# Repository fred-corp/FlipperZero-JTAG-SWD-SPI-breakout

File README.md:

# Flipper Zero JTAG/SWD/SPI breakout

A simple breakout board to connect a Flipper Zero to JTAG/SWD/SPI targets.

OSHW ID : [BE000022](https://certification.oshwa.org/be000022.html)

## Table of Contents

- [Features](#features)
  - [Compatible Apps](#compatible-apps)
  - [Pin selection](#pin-selection)
- [Pinouts](#pinouts)
  - [Flipper Zero GPIO header](#flipper-zero-gpio-header)
  - [20 pin JTAG 2x10 0.1" header](#20-pin-jtag-2x10-01-header)
  - [10 pin JTAG/SWD 2x5 0.1" and 0.05" header](#10-pin-jtagswd-2x5-01-and-005-header)
  - [6 pin SWD 2x3 0.1" header](#6-pin-swd-2x3-01-header)
  - [6 pin SPI 2x3 0.1" header](#6-pin-spi-2x3-01-header)
  - [5 pin UART 1x5 0.1" header](#5-pin-uart-1x5-01-header)
- [Usage](#usage)
- [Building Instructions](#building-instructions)
- [Sources](#sources)
- [License & Acknowledgements](#license--acknowledgements)

## Features

Convert the Flipper Zero's GPIO port into standard headers for JTAG, SWD, SPI, and UART connections.

### Compatible Apps

The board should be compatible with any apps that use the Flipper Zero's GPIO port for JTAG/SWD/SPI communication, though the following where the main targets during development for the pin selection and configuration :

- [DAP Link](https://lab.flipper.net/apps/dap_link) (JTAG/SWD & UART)
- [SWD Probe](https://lab.flipper.net/apps/swd_probe) (SWD)
- [SPI Mem Manager](https://lab.flipper.net/apps/spi_mem_manager) (SPI)
- [SPI-Terminal](https://lab.flipper.net/apps/flipper_spi_terminal) (SPI)
- [UART Terminal](https://lab.flipper.net/apps/uart_terminal) (UART)
- [ESP Flasher](https://lab.flipper.net/apps/esp_flasher) (UART)

> **Note** :  
Not all JTAG signals are used by the Flipper Zero apps, but the board can also be used to convert from a 20-pin ARM JTAG connector from another programmer to 10 or 6 pin headers.  
It can also be used as a SWD interface with the Flipper Zero as a target, by bridging the TCK and TMS signals to GPIO 10 and GPIO 12 via their corresponding solder jumpers. This enables programming/debugging the Flipper Zero itself with an external programmer.

### Pin selection

Depending on the app's requirements, some signals can be connected to different GPIO pins of the Flipper Zero using solder jumpers (see assembly instructions/schematics) :

- The TCK signal can be connected to GPIO 2 or GPIO 10
- The TMS signal can be connected to GPIO 3 or GPIO 12
- The UART TX pin can be connected to GPIO 13 or GPIO 15
- The UART RX pin can be connected to GPIO 14 or GPIO 16
- The SPI CS pin can be connected to GPIO 4

Other pins can be configured with jumper shunts :

- The VTref signal can be connected to 3.3V, 5V, or left floating
- The PWRSel signal can be connected to 5V or GND depending on the target's pinout
- The nTRST signal on the 10 pin headers can be connected to nTRST or left floating (NC)
- The SPI CS signal on the 6 pin SPI header can be connected to GPIO 4 or GPIO 6

## Pinouts

> Note : *Italic* pins are configurable with the solder jumpers

### Flipper Zero GPIO header

| Pin | Signals               |
|-----|-----------------------|
| 1   | 5V                    |
| 2   | SPI-SDO, *JTAG-TCK*   |
| 3   | SPI-SDI, *JTAG-TMS*   |
| 4   | *SPI-CS*, JTAG-nRESET |
| 5   | SPI-SCK, JTAG-TDO     |
| 6   | *SPI-CS*, JTAG-TDI    |
| 7   | NC                    |
| 8   | GND                   |
|     |                       |
| 9   | 3.3V                  |
| 10  | *JTAG-TCK*            |
| 11  | GND                   |
| 12  | *JTAG-TMS*            |
| 13  | *UART_TX*             |
| 14  | *UART-RX*             |
| 15  | *UART-TX*             |
| 16  | *UART-RX*             |
| 17  | NC                    |
| 18  | GND                   |

### 20 pin JTAG 2x10 0.1" header

| Signal    | Pin | Pin | Signal |
|-----------|-----|-----|--------|
| VTref     | 1   | 2   | NC     |
| nTRST     | 3   | 4   | GND    |
| TDI       | 5   | 6   | GND    |
| TMS       | 7   | 8   | GND    |
| TCK       | 9   | 10  | GND    |
| RTCK      | 11  | 12  | GND    |
| TDO       | 13  | 14  | GND    |
| nRESET    | 15  | 16  | GND    |
| NC        | 17  | 18  | GND    |
| 5V-Supply | 19  | 20  | GND    |

### 10 pin JTAG/SWD 2x5 0.1" and 0.05" header

| Signal     | Pin | Pin | Signal |
|------------|-----|-----|--------|
| VTref      | 1   | 2   | TMS    |
| GND        | 3   | 4   | TCK    |
| *PWRSel*   | 5   | 6   | TDO    |
| RTCK       | 7   | 8   | TDI    |
| *nTRST/NC* | 9   | 10  | nRESET |

### 6 pin SWD 2x3 0.1" header

| Signal | Pin | Pin | Signal |
|--------|-----|-----|--------|
| VTref  | 1   | 2   | TMS    |
| nRESET | 3   | 4   | TCK    |
| GND    | 5   | 6   | TDO    |

### 6 pin SPI 2x3 0.1" header

| Signal | Pin | Pin | Signal  |
|--------|-----|-----|---------|
| SDI    | 1   | 2   | VTref   |
| SCK    | 3   | 4   | SDO     |
| *CS*   | 5   | 6   | GND     |

The CS pin can be connected to GPIO 4 or GPIO 6 of the Flipper Zero, depending on the app's requirements.

### 5 pin UART 1x5 0.1" header

| Pin | Signal |
|-----|--------|
| 1   | 5V     |
| 2   | 3.3V   |
| 3   | TX     |
| 4   | RX     |
| 5   | GND    |

## Usage

> TODO : Add usage instructions for some Flipper Zero apps (e.G. DAP Link, SPI mem manager, etc.)

## Building Instructions

> TODO : Add assembly instructions and wiring diagrams from KiCAD sources (awaiting OSHWA certification).

## Sources

- [Flipper Zero Documentation](https://docs.flipperzero.one/)
- [Segger JTAG pinouts](https://www.segger.com/products/debug-probes/j-link/technology/interface-description/)
- [ARM JTAG/SWD pinouts](https://developer.arm.com/documentation/dui0499/d/ARM-DSTREAM-Target-Interface-Connections/)
- [AVR ISP pinouts](https://www.microchip.com/en-us/development-tool/atavrisp2)

## License & Acknowledgements

Made with ❤️, lots of ☕️, and lack of 🛌  
Published under CreativeCommons BY-SA 4.0

This work is licensed under a [Creative Commons Attribution-ShareAlike 4.0 International License](http://creativecommons.org/licenses/by-sa/4.0/).

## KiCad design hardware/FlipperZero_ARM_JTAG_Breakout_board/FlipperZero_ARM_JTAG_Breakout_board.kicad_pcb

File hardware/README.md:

# Hardware

This folder contains the KiCAD PCB Project files for the FlipperZero ARM JTAG breakout board.

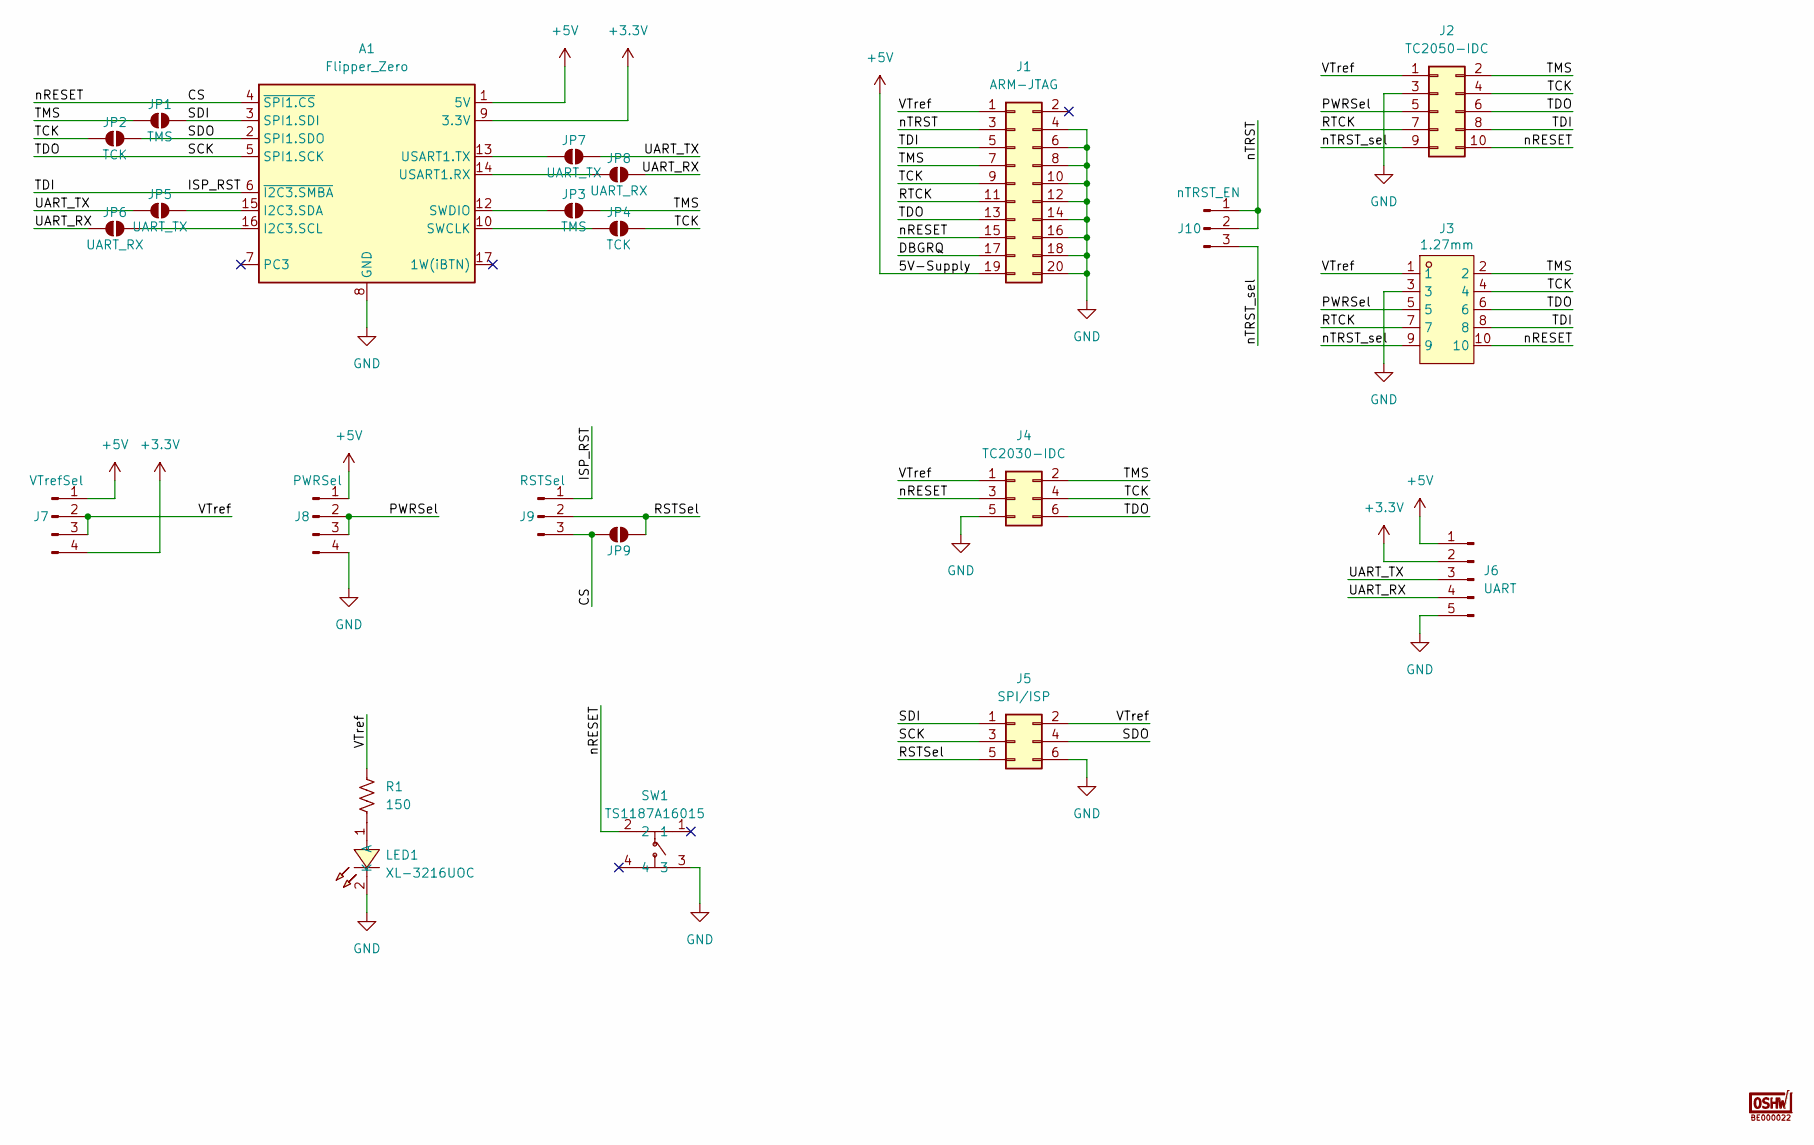
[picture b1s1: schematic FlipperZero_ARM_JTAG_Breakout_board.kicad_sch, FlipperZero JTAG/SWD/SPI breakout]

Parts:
A1: Flipper_Zero; Flipper_Zero_Straight
J1: ARM-JTAG; IDC-Header_2x10_P2.54mm_Vertical; LCSC Part C429961
J2: TC2050-IDC; IDC-Header_2x05_P2.54mm_Vertical; LCSC Part C429962
J3: 1.27mm; IDC-TH_10P-P1.27-V-M-R2-C5-S1.27; LCSC Part C50878437
J4: TC2030-IDC; IDC-Header_2x03_P2.54mm_Vertical; LCSC Part C4749192
J5: SPI/ISP; IDC-Header_2x03_P2.54mm_Vertical; LCSC Part C4749192
J6: UART; PinHeader_1x05_P2.54mm_Vertical
J7: VTrefSel; PinHeader_1x04_P2.54mm_Vertical
J8: PWRSel; PinHeader_1x04_P2.54mm_Vertical
J9: RSTSel; PinHeader_1x03_P2.54mm_Vertical
J10: nTRST_EN; PinHeader_1x03_P2.54mm_Vertical
JP1, JP3, JP9: TMS; JUMPER_SMD_1x2_tiny
JP2, JP4: TCK; JUMPER_SMD_1x2_tiny
JP5, JP7: UART_TX; JUMPER_SMD_1x2_tiny
JP6, JP8: UART_RX; JUMPER_SMD_1x2_tiny
LED1: XL-3216UOC; LED1206-R-RD_ORANGE; LCSC Part C965823
LOGO1: BE000022; OSHW-Certification-Mark-Stacked_8x7mm_SilkMask
R1: 150; R_0603_1608Metric_Pad0.98x0.95mm_HandSolder; LCSC Part C2907103
SW1: TS1187A16015; SW-SMD_4P-L5.2-W5.2-P3.70-LS6.4; LCSC Part C22375382

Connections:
+3.3V: A1.9 (3.3V), J6.2, J7.4
+5V: A1.1 (5V), J1.19, J6.1, J7.1, J8.1
/CS: A1.4 (~SPI1.CS), J1.15, J2.10, J3.10, J4.3, J9.3, JP9.1 (A), SW1.2
/DBGRQ: J1.17
/ISP_RST: A1.6 (~I2C3.SMBA), J1.5, J2.8, J3.8, J9.1
/PWRSel: J2.5, J3.5, J8.2, J8.3
/RSTSel: J5.5, J9.2, JP9.2 (B)
/RTCK: J1.11, J2.7, J3.7
/SCK: A1.5 (SPI1.SCK), J1.13, J2.6, J3.6, J4.6, J5.3
/SDI: A1.3 (SPI1.SDI), J5.1, JP1.1 (A)
/SDO: A1.2 (SPI1.SDO), J5.4, JP2.1 (A)
/TCK: J1.9, J2.4, J3.4, J4.4, JP2.2 (B), JP4.2 (B)
/TMS: J1.7, J2.2, J3.2, J4.2, JP1.2 (B), JP3.2 (B)
/UART_RX: J6.4, JP6.2 (B), JP8.2 (B)
/UART_TX: J6.3, JP5.2 (B), JP7.2 (B)
/VTref: J1.1, J2.1, J3.1, J4.1, J5.2, J7.2, J7.3, R1.1
/nTRST: J1.3, J10.1, J10.2
/nTRST_sel: J2.9, J3.9, J10.3
GND: A1.8 (GND), A1.11 (GND), A1.18 (GND), J1.4, J1.6, J1.8, J1.10, J1.12, J1.14, J1.16, J1.18, J1.20, J2.3, J3.3, J4.5, J5.6, J6.5, J8.4, LED1.2 (K), SW1.3
unnamed: A1.16 (I2C3.SCL), JP6.1 (A)
unnamed: A1.15 (I2C3.SDA), JP5.1 (A)
unnamed: A1.10 (SWCLK), JP4.1 (A)
unnamed: A1.12 (SWDIO), JP3.1 (A)
unnamed: A1.14 (USART1.RX), JP8.1 (A)
unnamed: A1.13 (USART1.TX), JP7.1 (A)
unnamed: LED1.1 (A), R1.2

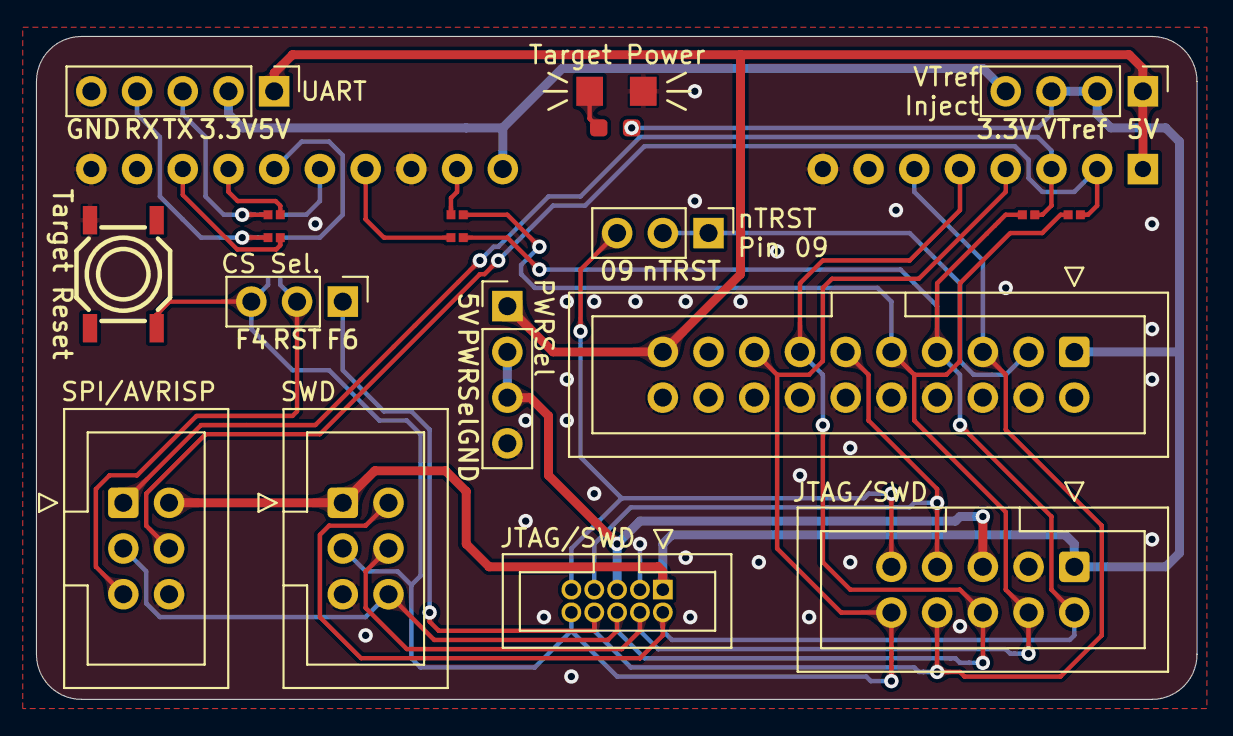
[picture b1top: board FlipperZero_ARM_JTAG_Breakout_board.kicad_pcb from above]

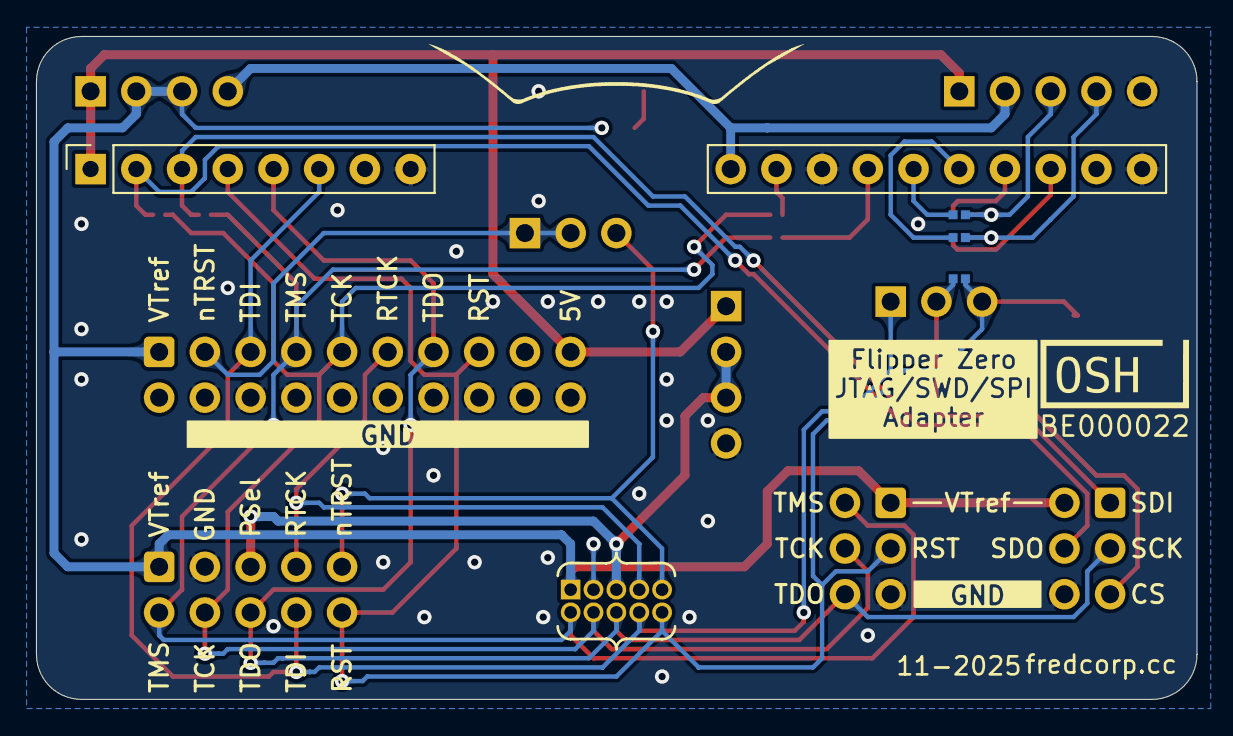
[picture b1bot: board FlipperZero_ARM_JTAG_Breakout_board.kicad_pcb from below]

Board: 2 copper layers, 64.5 x 36.8 mm, 24 parts (5 on the bottom side), 25 nets.

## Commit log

2025-11-10 added trinity of git repo files
2025-11-10 added files to gitignore
2025-11-10 added hardware folder
2025-11-10 added KiCAD sources
2025-11-10 added OSHW footprint template
2025-11-10 added structure to readme
2025-11-10 added .github folder
2025-11-10 updated signal names for up-to-date terminology
2025-11-10 updated footprint & ran DRU check
2025-11-11 added header pinouts
2025-11-11 added sources
2025-11-11 added compatible apps, flipper GPIO pinout, UART pinout
2025-11-11 fix: correct formatting and terminology for Flipper Zero references in README
2025-11-11 updated app links to use their Flipper Lab page
2025-11-11 added jumpers on 3D models, fixed silkscreen names
2025-11-11 added PCB render image in README
2025-11-11 added PCB front and back render images to README
2025-11-11 Fixed typo in silkscreen
2025-11-14 added OSHWA Certification ID
2025-11-14 removed rounded tracks version
2025-11-14 updated gitignore
2025-11-14 added fabrication files
2025-11-14 updated renders
2025-11-14 final save
